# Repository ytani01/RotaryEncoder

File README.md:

Rotary Encoder
====

## Description
ロータリーエンコーダー用クラス

## Class
pin_rot = [pin1, pin2]

RotaryEncoder(pin_rot, rot_callback, pin_sw, sw_callback)

RotaryKey(pin_rot, pin_sw, rk_callback)

## Hardware

[https://www.amazon.co.jp/dp/B014VUOP7S/]

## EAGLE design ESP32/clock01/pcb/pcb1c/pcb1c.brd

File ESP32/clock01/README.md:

#

## 設定

### ArduinoIDE

#### ライブラリ

- Adafruit BME280
- FastLED
- PubSubClient by Nick O’Lear

#### 設定

- ボード: ESP32 Dev Module or ESP32 PICO-D4

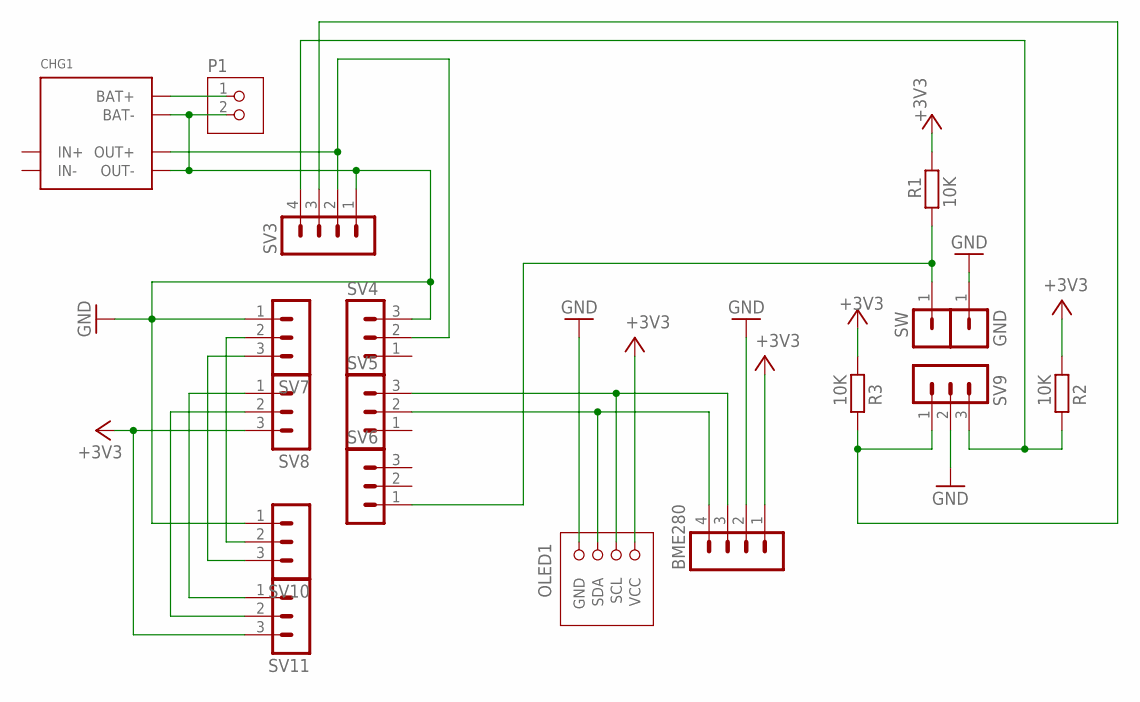
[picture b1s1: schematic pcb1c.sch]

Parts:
BME280: PINHEAD-MA04-1
CHG1: TP4056MOD2-TYPE-C
GND: PINHEAD-MA01-1
OLED1: OLED-SSD1306-0.96; OLED-I2C-0.96
P1: JST-PH2
R1, R2, R3: 10K; 0204/5
SV3: PINHEAD-MA04-1
SV4, SV5, SV6, SV7, SV8, SV9, SV10, SV11: PINHEAD-MA03-1
SW: PINHEAD-MA01-1

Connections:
+3V3: BME280.1, OLED1.VCC, R1.2, R2.1, R3.1, SV8.3, SV11.3
GND: BME280.2, CHG1.BAT-, CHG1.OUT-, GND.1, OLED1.GND, P1.2, SV3.1, SV4.3, SV7.1, SV9.2, SV10.1
unnamed: R3.2, SV3.3, SV9.1
unnamed: BME280.3, OLED1.SCL, SV5.3
unnamed: BME280.4, OLED1.SDA, SV5.2
unnamed: SV7.2, SV10.2
unnamed: CHG1.OUT+, SV3.2, SV4.2
unnamed: R2.2, SV3.4, SV9.3
unnamed: SV7.3, SV10.3
unnamed: SV8.1, SV11.1
unnamed: SV8.2, SV11.2
unnamed: R1.1, SV6.1, SW.1
unnamed: CHG1.BAT+, P1.1

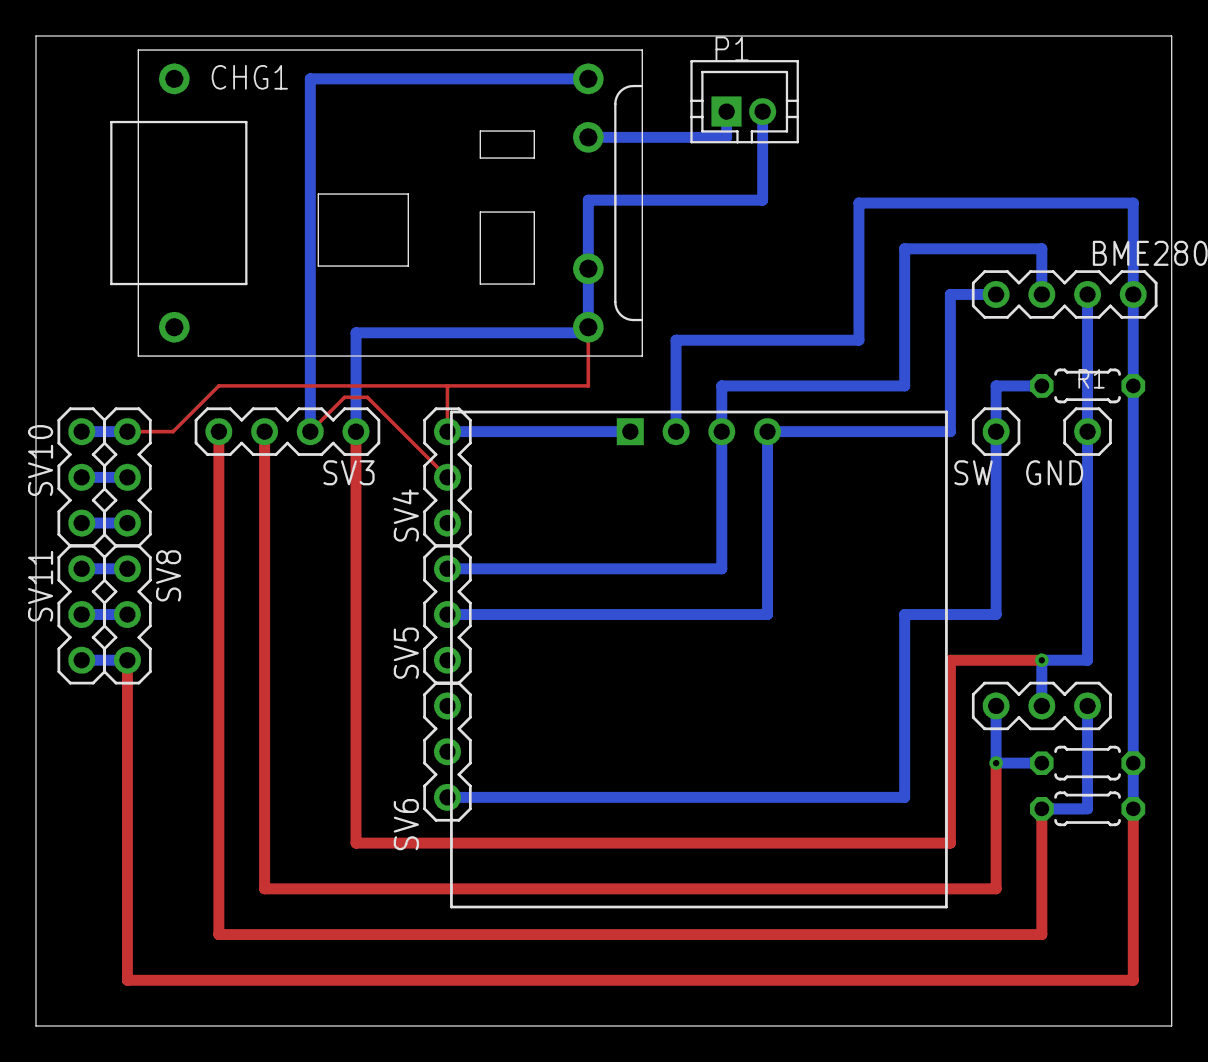
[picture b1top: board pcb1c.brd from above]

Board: 2 copper layers, 63.1 x 55.0 mm, 18 parts (0 on the bottom side), 13 nets.

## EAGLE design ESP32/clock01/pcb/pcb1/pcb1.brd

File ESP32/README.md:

# Rotary Encoder Library for ESP32
ESP32用ロータリー・エンコーダー・ライブラリ

## Description

* ESP32のパルスカウンター(PCNT)を利用
* マルチタスクで実装しているが、簡単に利用できる
* Queueを利用しているため、タイミングの制御が不要

## Sample code

## Test Program

## 注意事項

### タイマーは、Tickerを使う

``xTimer..()``のタイマーは、なぜかコールバック実行中に、
OLEDの``display()``が、異様に遅くなる(460ms程度 .. 通常は50ms以下)。

Tickerの場合、この問題は起きない。

### OLED(SSD1306) と BME280 の同時利用に注意！ .. マルチタスクできない!?

* もしかして、I2Cライブラリがスレッドセーフじゃない???
* OLED と BME280 は、同じタスクにする。
* この場合、BME280を``FORCED``にすると遅延が生じるので、
  使わない方がよい。
* さらにこの場合、温度が高めにでるので、-1℃ぐらい(?)の補正が必要。

## 要検討

### 戻り値が、``pdPASS``だったり、``pdTRUE``だったり..

### TWDT(Task WatchDoc Timer)

タスク毎にTWDT時間を調整しようとしたが、今回は見送り

参考コード(検討中)
```
#include <esp_task_wdt.h>
:
void task_net_mgr() {
  ESP_ERROR_CHECK(esp_task_wdt_init(60, true)); // *** 60sec
  ESP_ERROR_CHECK(esp_task_wdt_add(NULL));      // *** 必要(?)
  :
  while (true) { // main loop
    :
    ESP_ERROR_CHECK(esp_task_wdt_reset());      // *** 必要(?)
    delay(1)                // *** コンテキスト・スイッチのために必要(?)
  } // main loop
} // task_net_mgr()
```

## Reference

* Character codes

* Algorithm to convert RGB to HSV and HSV to RGB in range 0-255 for both
https://stackoverflow.com/questions/3018313/algorithm-to-convert-rgb-to-hsv-and-hsv-to-rgb-in-range-0-255-for-both

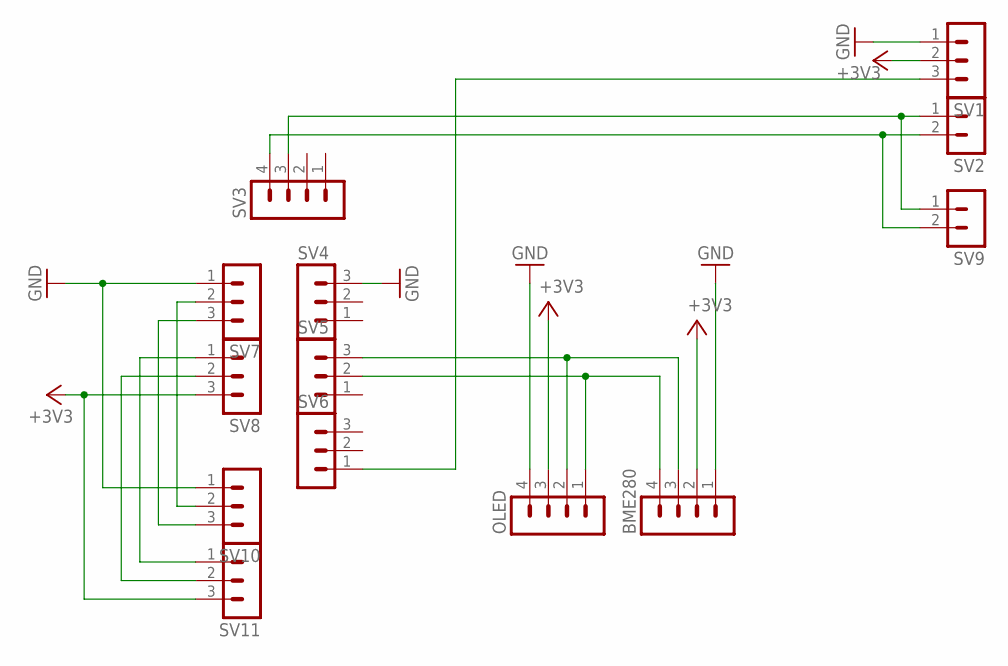
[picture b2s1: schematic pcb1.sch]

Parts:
BME280: PINHEAD-MA04-1
OLED: PINHEAD-MA04-1
SV1, SV4, SV5, SV6, SV7, SV8, SV10, SV11: PINHEAD-MA03-1
SV2, SV9: PINHEAD-MA02-1
SV3: PINHEAD-MA04-1

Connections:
+3V3: BME280.2, OLED.3, SV1.2, SV8.3, SV11.3
GND: BME280.1, OLED.4, SV1.1, SV4.3, SV7.1, SV10.1
unnamed: SV1.3, SV6.1
unnamed: BME280.3, OLED.2, SV5.3
unnamed: BME280.4, OLED.1, SV5.2
unnamed: SV7.2, SV10.2
unnamed: SV2.2, SV3.4, SV9.2
unnamed: SV2.1, SV3.3, SV9.1
unnamed: SV7.3, SV10.3
unnamed: SV8.1, SV11.1
unnamed: SV8.2, SV11.2

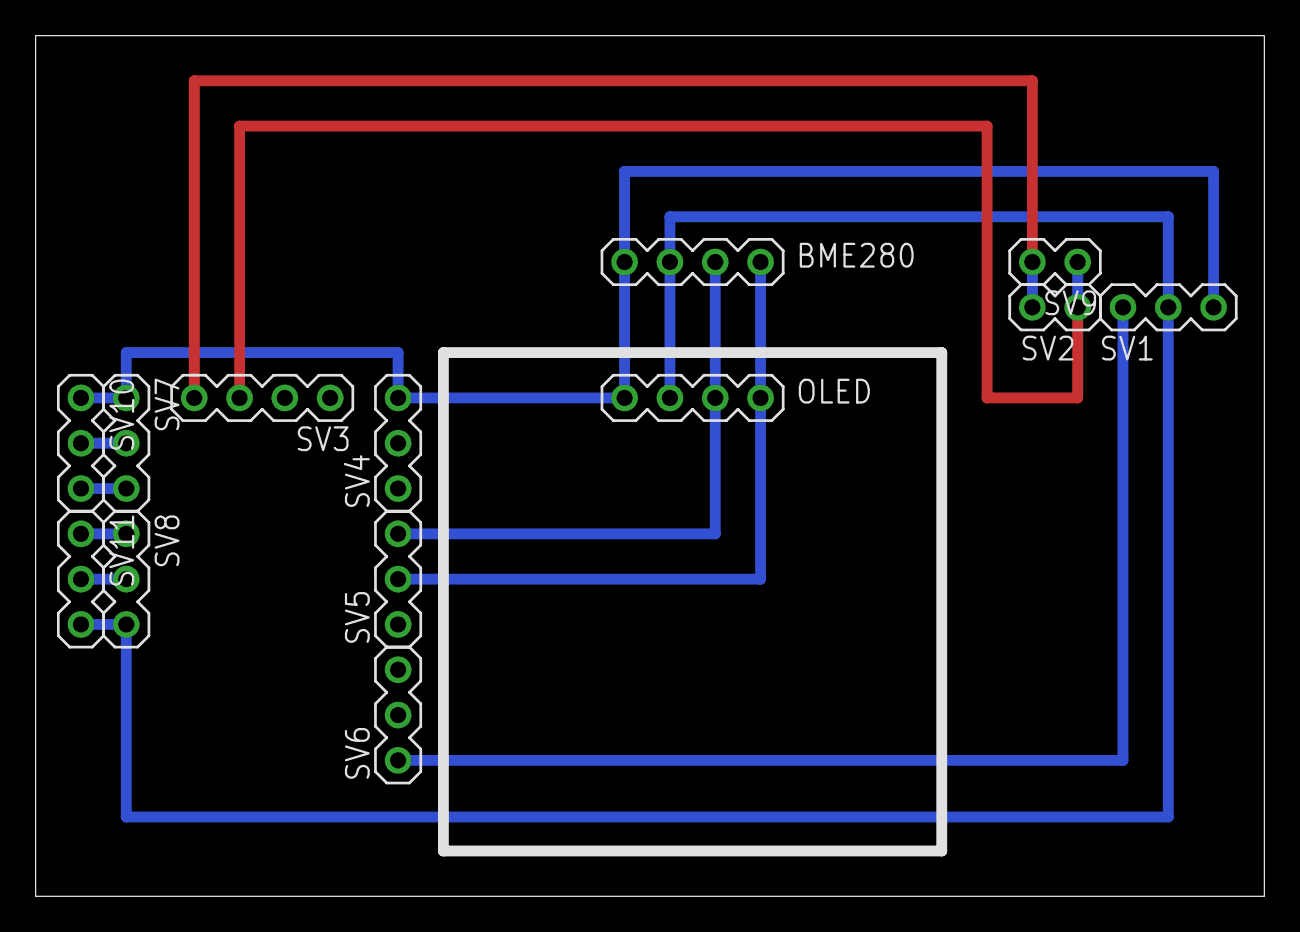
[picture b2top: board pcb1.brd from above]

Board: 2 copper layers, 68.9 x 48.2 mm, 13 parts (0 on the bottom side), 11 nets.

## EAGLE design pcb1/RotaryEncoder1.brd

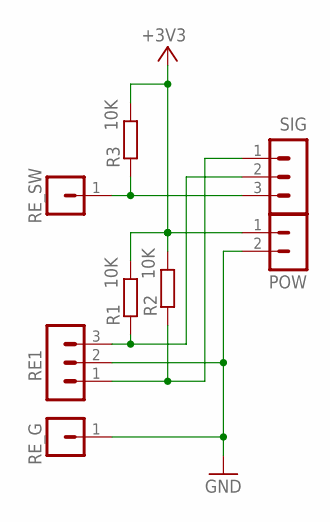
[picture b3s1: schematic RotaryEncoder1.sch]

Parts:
POW: PINHEAD-MA02-1
R1, R2, R3: 10K; 0204/5
RE1: PINHEAD-MA03-1
RE_G: PINHEAD-MA01-1
RE_SW: PINHEAD-MA01-1
SIG: PINHEAD-MA03-1

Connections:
+3V3: POW.1, R1.1, R2.2, R3.1
GND: POW.2, RE1.2, RE_G.1
unnamed: R3.2, RE_SW.1, SIG.3
unnamed: R1.2, RE1.3, SIG.2
unnamed: R2.1, RE1.1, SIG.1

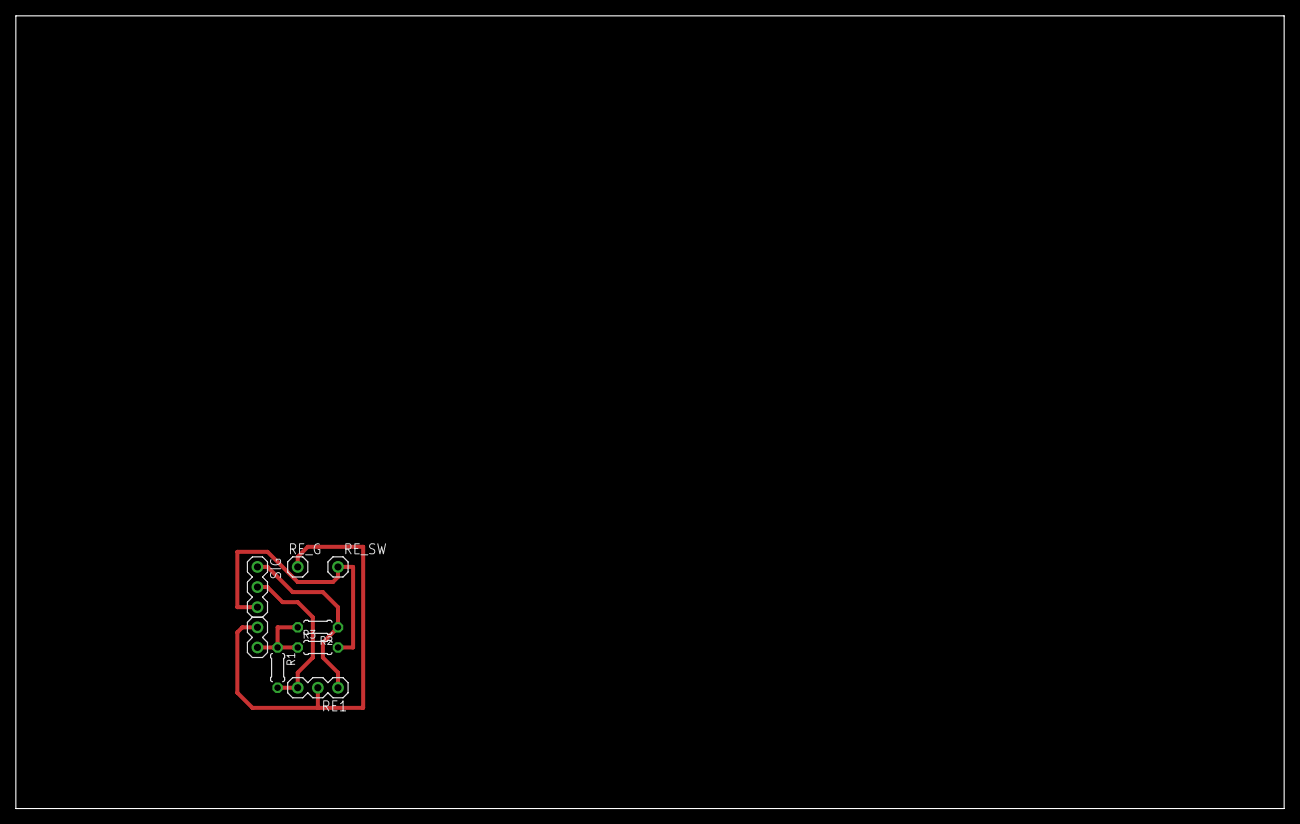
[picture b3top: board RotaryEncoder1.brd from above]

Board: 2 copper layers, 160.0 x 100.0 mm, 8 parts (0 on the bottom side), 5 nets.

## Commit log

2022-01-23 ADD: ESP32/test1/
2022-01-23 ADD: ESP32/test1/Esp32PcntRotaryEncoder.*
2022-01-23 ADD: ESP32/test2/ (MultiTask, FastLED)
2022-01-23 ADD: ESP32/test3/ (MultiTask, FastLED, WiFi)
2022-01-24 UPD: ESP32/test3/ (MultiTask, FastLED, WiFi)
2022-01-24 UPD: ESP32/test3/ (MultiTask, FastLED, WiFi, Button)
2022-01-24 UPD: ESP32/test4/ (MultiTask, Timer, FastLED, WiFi, Button, OLED)
2022-01-24 UPD: ESP32/README.md
2022-01-25 UPD: test4
2022-01-25 UPD: ESP32/test4/
2022-01-27 ADD: ESP32/test5/
2022-01-27 ADD: ESP32/test6/
2022-01-28 UPD: test6/
2022-01-28 UPD: ESP32/test6/
2022-01-29 UPD: ESP32/test7/
2022-01-29 START: ESP32/test8/
2022-01-29 UPD: ESP32/test8/
2022-01-30 UPD: ESP32/test9/
2022-01-30 START: ESP32/test10/
2022-01-30 UPD: ESP32/test10/
2022-01-31 UPD: ESP32/README.md ESP32/test10/
2022-01-31 START: ESP32/test11/
2022-02-01 UPD: ESP32/test11/
2022-02-02 START: ESP32/test12/
2022-02-03 UPD: ESP32/test12/
2022-02-04 UPD: ESP32/test12/: blink
2022-02-04 UPD: ESP32/test13/
2022-02-04 ADD: ESP32/test14/: OledMenu
2022-02-05 ADD: ESP32/test15/
2022-02-06 UPD: ESP32/test15/: use vector
2022-02-06 UPD: ESP32/test15/: ToDo: class OledMenuEnt
2022-02-06 ADD: ESP32/test16/: ToDo: class OledMenuEnt
2022-02-06 UPDlf: ESP32/test16/: ToDo: class OledMenuEnt
2022-02-07 UPD: ESP32/test16/: class OledMenu
2022-02-07 UPD: ESP32/test16/
2022-02-08 UPD: test16/
2022-02-08 ADD: ESP32/test20/
2022-02-09 UPD: test20/
2022-02-10 UPD: ESP32/test20/
2022-02-10 START: ESP32/test21/
2022-02-10 UP: ESP32/test21/ restart WiFi
2022-02-11 UPD: ESP32/test22/: OLED_MENU_DST_TYPE_TEXT
2022-02-11 UPD: ESP32/test22/: NaN temp etc.
2022-02-11 ADD: ESP32/test22/: SetTempOffsetMode
2022-02-11 ADD: ESP32/test22/: clear_ssid
2022-02-11 UPD: ESP32/test22/: clear_ssid
2022-02-11 UPD: ESP32/test22/
2022-02-11 UPD: ESP32/test22/: display FPS
2022-02-12 START: ESP32/test23/
2022-02-12 START: ESP32/test30/
2022-02-12 UPD: ESP32/test30/
2022-02-13 START: ESP32/test31/
2022-02-14 UPD: ESP32/test31/
2022-02-14 UPD: ESP32/test31/: set SSID and Password
2022-02-15 UPD: test31/: save Temperature Offset
2022-02-16 START: ESP32/test32/
2022-02-16 UPD: ESP32/test32/: file names
2022-02-16 UPD: ESP32/test32/: save multi SSIDs
2022-02-17 START: ESP32/test33/
2022-02-17 START: ESP32/test33/: WiFi
2022-02-17 START: ESP32/test34/
2022-02-18 ADD: ESP32/test34/: MQTT Publisher
2022-02-19 UPD: ESP32/test34/: MQTT Publisher
2022-02-19 START: ESP32/test35/
2022-02-19 UPD: ESP32/test35/: RotaryEncoderText
2022-02-20 UPD: ESP32/test35/
2022-02-20 ADD: ESP32/pcb1
2022-02-20 UPD: ESP32/pcb1
2022-02-20 START: ESP32/test36
2022-02-20 UPD: ESP32/test36
2022-02-21 ADD: ESP32/pcb1a/
2022-02-21 UPD: ESP32/pcb1a/
2022-02-22 START: ESP32/test37/
2022-02-22 UPD: ESP32/test37/: ScanSsidMode and more
2022-02-24 ADD: ESP32/pcb1b/
2022-02-24 UPD: ESP32/test37/: for pcb1b
2022-02-24 UPD: ESP32/test37/: drawTemp()
2022-02-25 UPD: ESP32/test37/: publish_interval
2022-02-25 UPD: ESP32/test37/: temperature interval
2022-02-27 START: ESP32/test38/
2022-02-27 UPD: ESP32/test38/
2022-02-27 ADD: ESP32/pcb1c/
2022-02-28 UPD: ESP32/pcb1c/
2022-02-28 UPD: ESP32/test38/: blink
2022-03-05 ADD: ESP32/pcb1d/
2022-03-06 UPD: test38/
2022-03-07 UPD: ESP32/pcb1d/base2.svg
2022-03-11 START: ESP32/test39/
2022-03-13 ADD: test0/
2022-03-14 UPD: test39/
2022-03-14 UPD: test39/: idle reset
2022-03-23 UPD: test39/: NTP sync mode etc
2022-03-23 UPD: test39/: VERSION_STR
2022-03-26 pcb1e
2022-03-28 pcb1f
2022-05-26 ADD: ESP32/pcb2/
2022-05-27 UPD: ESP32/pcb2/
2022-05-29 UPD:ESP32/pcb2/
2023-02-03 ADD: test39/README.md
2023-04-10 clock01/
2023-04-10 TBD: clock01/
2023-04-11 UPD: test/ --> tests/
2023-04-12 UPD: test101: multi task
2023-04-14 UPD: test101
2023-04-15 UPD: test101/Mode
2023-04-25 UPD: commonlib: get_mac_addr* funcs
2023-04-25 UPD: NetMgr
2023-04-27 UPD: Ntp
2023-04-28 UPD: Mode_Main:loop()
2023-04-28 UPD: Conf
2023-04-29 UPD: display
2023-04-29 ADD: Task_ScanSsid
2023-09-24 FIX: test101/Task_ScanSsid.cpp
